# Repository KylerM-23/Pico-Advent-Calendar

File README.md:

# Pico-Advent-Calendar

## Introduction
The 25 Days of Makermas is a Raspberry Pi Pico kit consiting of 25 projects that serve as an introduction to programming and controlling devices with a Raspberry Pi Pico. </br>

[Booklet WIP](https://docs.google.com/document/d/1rmNjlnt3vpmemfZ5pnnCj9qUnz_O2xRp1bQ-7SMrb30/edit?usp=sharing) </br> </br> 
</br> 
 
## Parts Included:

| Item                           | Quantity | | Item                           | Quantity |
| ------------------------------ | -------- |-| ------------------------------ | -------- |
| Pi Pico                        | 1        | | Large Button                   | 3        |
| Makermas PCB                   | 1        | | Large Button Caps              | 3        |
| Wire M-F                       | 1        | | Slide Switch                   | 3        |
| Wire F-F                       | 1        | | Common Anode RGB LED           | 3        |
| Wire M-M                       | 1        | | White LED                      | 10       |
| 10k Potentiometer              | 2        | | Green LED                      | 10       |
| 180 Degree Servo Motor         | 1        | | HC-SR04 Ultrasonic Sensor      | 1        |
| 2.2K Resistors                 | 20       | | PIR Motion Sensor HC-SR501     | 1        |
| 10k Resistors                  | 4        | | TMP1075 I2C Module             | 1        |
| 10k Photoresistor              | 2        | | 1602 I2C LCD                   | 1        |
| 10k Thermistor                 | 2        | | Capacitive Touch Sensor Module | 1        |
| Common Anode 7-Segment Display | 2        | | 16 Pin IC Sockets              | 3        |
| 220 Ohm Resistor Array         | 4        | | 2 Pin Male Header              | 2        |
| SN74HC595 IC                   | 3        | | 2 Pin Jumper                   | 2        |
| 0.1uF Capacitor                | 4        | | 3 Pin Male Header              | 4        |
| Passive (Transducer) Buzzer    | 2        | | Popsicle Stick                 | 3        |
| Active (Indicator) Buzzer      | 2        | | Rubber Band                    | 3        |
| Small Button                   | 10       | | Micro USB Cable                | 1        |
| 3 Pin Female Header            | 2        | | 4 Pin Male Header              | 3        |
| 4 Pin Female Header            | 3        | | 5 Pin Female Header            | 3        |
| 20 Pin Female Header           | 3        | | 5 Pin Female Header            | 5        |
| Nylon Standoffs M3 x 20MM      | 5        |

## Table of Contents
- [Day 1](#day1)
- [Day 2](#day2)
- [Day 3](#day3)
- [Day 4](#day4)
- [Day 5](#day5)
- [Day 6](#day6)
- [Day 7](#day7)
- [Day 8](#day8)
- [Day 9](#day9)
- [Day 10](#day10)
- [Day 11](#day11)
- [Day 12](#day12)
- [Day 13](#day13)
- [Day 14](#day14)
- [Day 15](#day15)
- [Day 16](#day16)
- [Day 17](#day17)
- [Day 18](#day18)
- [Day 19](#day19)
- [Day 20](#day20)
- [Day 21](#day21)
- [Day 22](#day22)
- [Day 23](#day23)
- [Day 24](#day24)
- [Day 25](#day25)

## Day 1: Setup 
1. [Thonny IDE](#day1_thonny)
   1. Install Thonny
   2. Download Pi Pico Firmware
   3. Run Test Program
2. [The Pi Pico Pinout](#day1_pinout)
   1. Pinout
   2. Identify GPIO pin for LED
3. [Controlling the onboard LED](#day1_demo)
  
### Thonny IDE 
Go to the [Thonny](https://thonny.org/) website and download the free IDE. Thonny was chosen because it has features that make it easier to program with the pico and installing the firmware.

After opening Thonny, go to _Run_ -> _Configure Interpreter_                                                                   </br> </br> 
From the Interpreter Menu Select _MicroPython (Raspberry Pi Pico)_ and click on __Install or update MicroPython__              </br>  </br> 
Copy the following settings to install the Pi Pico Firmware. _If you have a different Pico model, choose the proper variant._  </br> </br> 

The Pico should be ready to go. </br>

We can now use the shell and write the hardest line of code ever. </br> </br> 

### Pico Pinout  
Microcontrollers have multiple pins that have multiple functions on each. Most pins are general purpose input outpute (GPIO) pins that can be configure to output signals/data or input (recieve) signals/data. The other pins are power pins or serve special functions.
 - The power pins are VBUS (5V from the USB), 3V3 (3.3V), and GND. The other pins are power input or other functons.

Many of the GPIO pins have multiple functions that can only be used on that pin. For example Pin 32 has GP27, ADC1, and I2C1 SDA for its functions. Programmers can choose which function they want to use on each pin. How you use each pin will vary on what pin functions you need.
- For example if you need a lot of ADC functions, it may be better to use another pin's I2C function and dedicate Pin 32 to ADC.

The image below shows all the pins on the pico with their respective features. </br>  </br> 

### Controlling the onboard LED 
Day1.py toggles the onboard LED and you can vary the speed at which the LED blinks. If you make the time fast enough the LED will appear constantly illuminated and you cannot see it turning off.

</br> 

## Day 2: Soldering 
Day 2 introduces the main PCB and the header pins, and LED Checker/ Status Light are soldered in.

</br> 

## Day 3: Controlling an External LED 
Day 3 invovles controlling an LED with the GPIO pins and explaining GPIO pins in a little more detail in addition to the various methods to control the LED.

</br> 

## Day 4: Reading Inputs From a Button 
Day 4 continues the basics of GPIO inputs covering digital logic levels and reading inputs from a push button.

</br> 

## Day 5: Slide Switch 
Day 5 introduces slide switches and using internal pull-up/down resistors.

</br> 

## Day 6: Active Buzzer 
Day 6 introduces buzzers and how they create sound.

</br> 

## Day 7: Capacitive Touch Sensor 
Day 7 introduces capacitive touch sensors and uses them to create a tapping game. Interrupts are introduced here.

</br> 

## Day 8: RGB LED 
Day 8 introduces RGB LEDs and LED configurations like common anode. The first class is created here.

</br> 

## Day 9: Button Matrix 
Day 9 sees the creation of a class to handle reading the inputs of 4 buttons.

</br> 

## Day 10: Simon Says 
Day 10 is the first big system lesson that has the button matrix, RGB LED, and buzzer used to create a game of simon says!

</br> 

## Day 11: Analog Inputs With a Potentiometer 
Day 11 introduces analog inputs and reading them with the ADC on the pico. A potentiometer is measured as an example.

</br> 

## Day 12: PWM 
Day 12 introduces PWM and how to creates an effective analog voltage for us to control devices like an LED.

</br> 

## Day 13: Rainbow RGB LED 
Day 13 sees PWM used with the RGB LED to create various colors and sweep through the visible color spectrum.

</br> 

## Day 14: Servo Motor 
Day 14 utilizes PWM to control a servo motor and walks through the process of creating the code needed to control PWM devices.

</br> 

## Day 15: Passive Buzzer 
Day 15 sees the user creating a music by using PWM to produce different pitched notes.

</br> 

## Day 16: PIR Motion Sensor 
Day 16 introduces a PIR motion sensor and uses it to detect motion nearby.

</br> 

## Day 17: Ultrasonic Sensor 
Day 17 introduces the ultrasonic distance sensor.

</br> 

## Day 18: Proimity Gate 
Day 18 allows the user to create an arm gate that opens when the ultrasonic sensor and or motion sensor detect someone approaching it. Day 18 comes with a popsicle stick and rubber band to create the "arm".

</br> 

## Day 19: Photoresistor 
Day 19 introduces the photoresistor and how to estimate the amount of light to control other devices.

</br> 

## Day 20: Thermistor 
Day 20 introduces the thermistor and how to measure the ambient temperature.

</br> 

## Day 21: Snowflake Display 
Day 21 introduces the 74HC595 shift register to control multiple LEDs (snowflake display) with less pins. 

</br> 

## Day 22: 7-Segment Display 
Day 22 has the user daisy chain shift registers to control multiple LED displays. The LED display for ths lesson is a 7-segment display.

</br> 

## Day 23: TMP1075 
Day 23 introduces I2C devices and uses the TMP1075 to measure temperature.

</br> 

## Day 24: 1602 LCD 
Day 24 introduces the 1602 LCD and using multiple I2C devices on the same bus.

</br> 

## Day 25: Spread Holiday Cheer 
On Day 25 you must express your holiday cheer. How you do so is left to you. You have plenty of tools. Good luck! </br>
To give you a place to start. One idea is to have a light show with the snowflake display while Christmas music plays on the buzzer (you can also control both buzzers).

</br> 
#Thanks
This project is ongoing and will likely continue to change. Thanks for checking it out.

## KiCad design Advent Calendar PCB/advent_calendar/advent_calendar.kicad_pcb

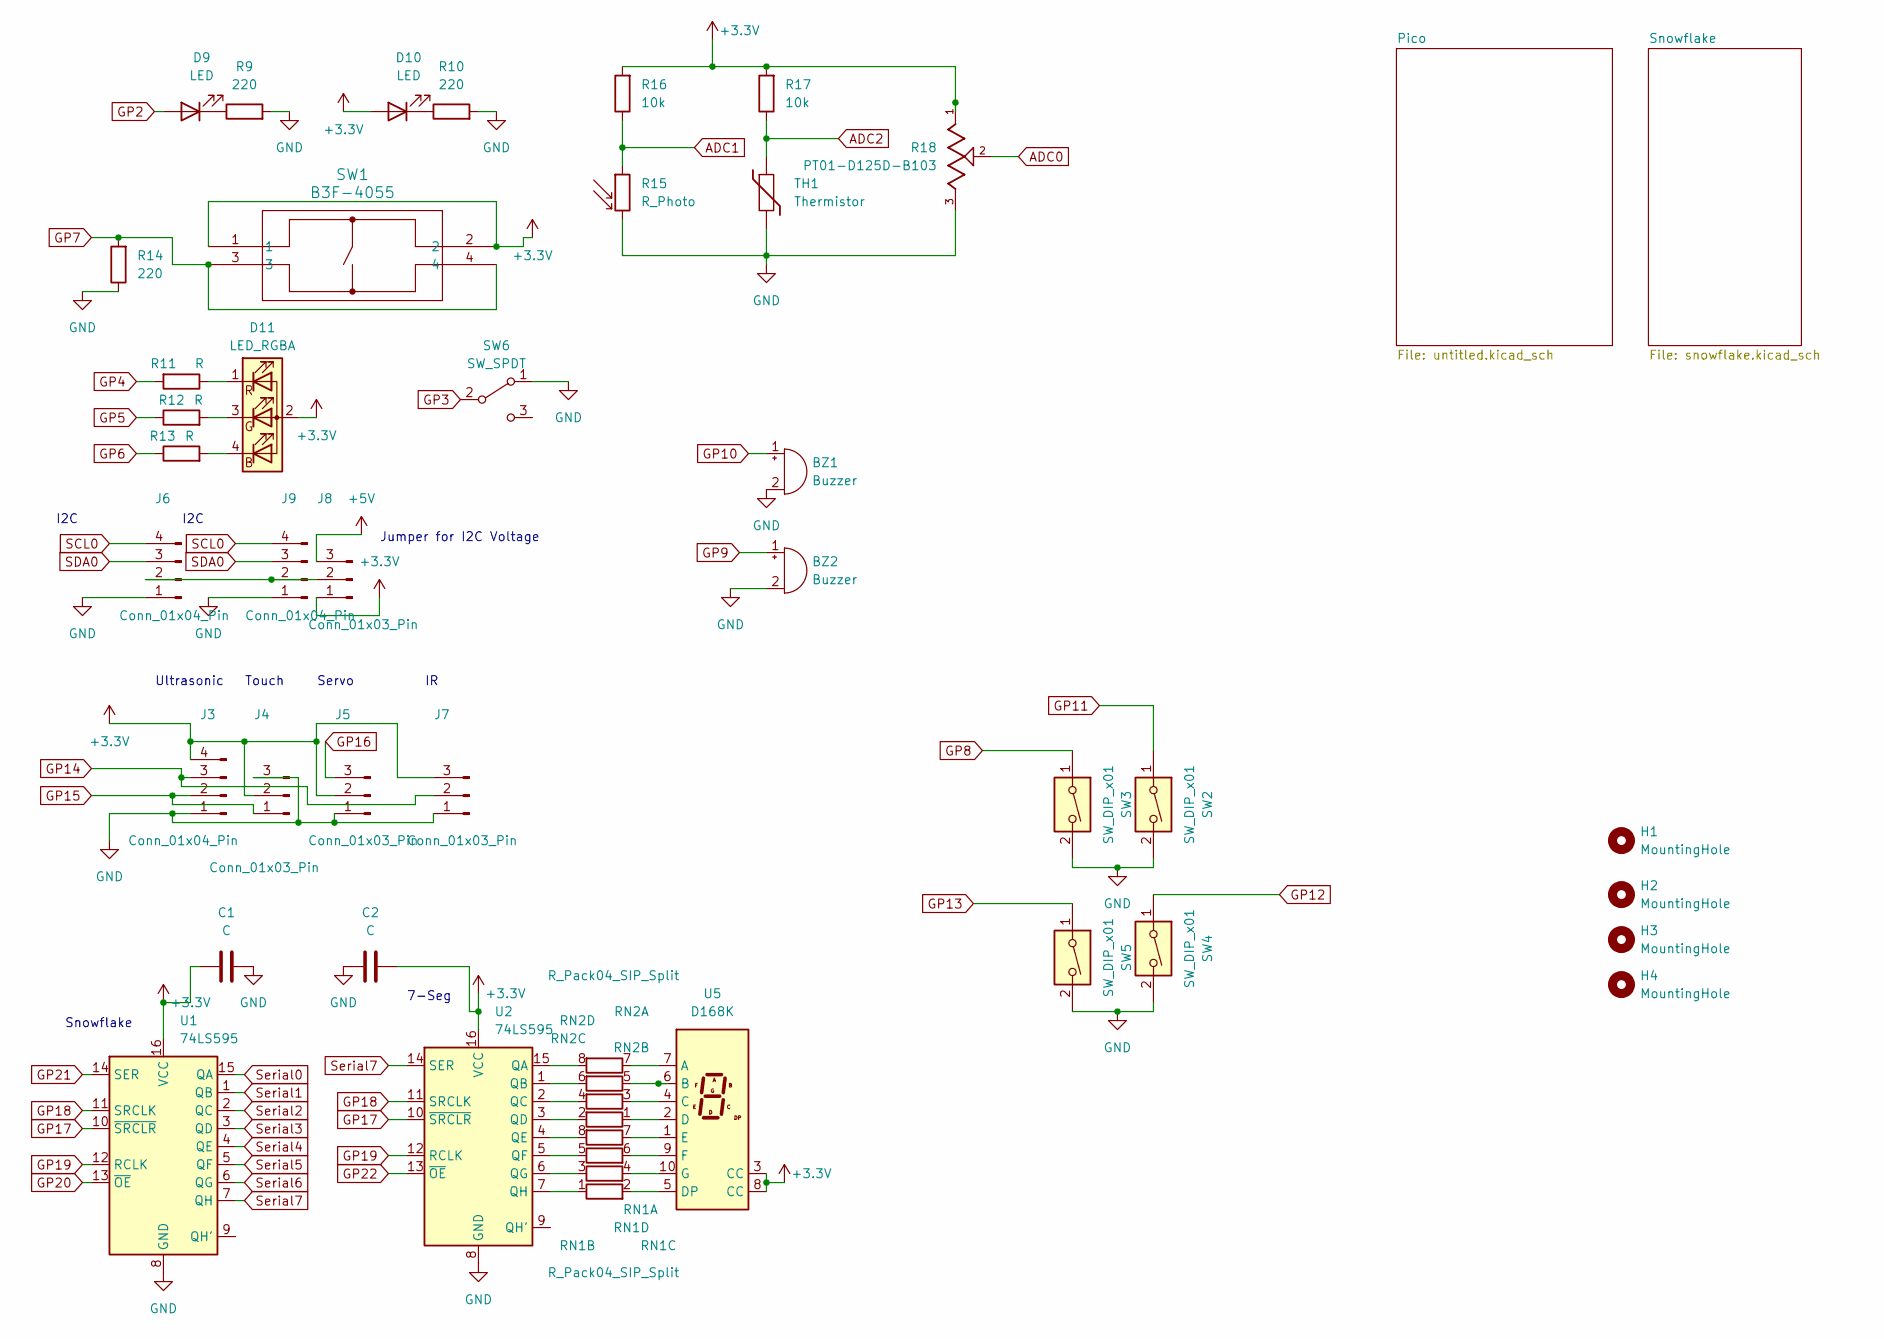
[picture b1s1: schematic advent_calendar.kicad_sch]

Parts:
BZ1, BZ2: Buzzer; Buzzer_12x9.5RM7.6
C1, C2: C; C_Rect_L4.0mm_W2.5mm_P2.50mm
D9, D10: LED; LED_D5.0mm
D11: LED_RGBA; LED_D5.0mm-4_RGB_Wide_Pins
H1, H2, H3, H4: MountingHole; MountingHole_3mm
J3, J6, J9: Conn_01x04_Pin; PinHeader_1x04_P2.54mm_Vertical
J4, J5, J7, J8: Conn_01x03_Pin; PinHeader_1x03_P2.54mm_Vertical
R9, R10, R14: 220; R_Axial_DIN0207_L6.3mm_D2.5mm_P10.16mm_Horizontal
R11, R12, R13: R; R_Axial_DIN0207_L6.3mm_D2.5mm_P10.16mm_Horizontal
R15: R_Photo; R_LDR_7x6mm_P5.1mm_Vertical
R16, R17: 10k; R_Axial_DIN0207_L6.3mm_D2.5mm_P10.16mm_Horizontal
R18: PT01-D125D-B103; TRIM_PT01-D125D-B103; PARTREV 1.0
RN1, RN2: R_Pack04_SIP_Split; R_Array_SIP8
SW1: B3F-4055; SW_B3F-4050_OMR
SW2, SW3, SW4, SW5: SW_DIP_x01; SW_PUSH_6mm
SW6: SW_SPDT; PinHeader_1x03_P2.54mm_Vertical
TH1: Thermistor; PinHeader_1x02_P2.54mm_Vertical
U1, U2: 74LS595; DIP-16_W7.62mm
U5: D168K; D1X8K

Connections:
+3.3V: C1.1, C2.2, D10.2 (A), D11.2, J3.4, J4.2, J5.2, J7.3, J8.1, R16.2, R17.2, R18.1, SW1.1, SW1.2, U1.16 (VCC), U2.16 (VCC), U5.3 (CC), U5.8 (CC); also elsewhere on the board
+5V: J8.3; also elsewhere on the board
ADC0: R18.2; also elsewhere on the board
ADC1: R15.1, R16.1; also elsewhere on the board
ADC2: R17.1, TH1.1; also elsewhere on the board
GND: BZ1.2 (+), BZ2.2 (+), C1.2, C2.1, J3.1, J4.3, J5.1, J6.1, J7.1, J9.1, R9.2, R10.2, R14.1, R15.2, R18.3, SW2.2, SW3.2, SW4.2, SW5.2, SW6.1 (A), TH1.2, U1.8 (GND), U2.8 (GND); also elsewhere on the board
GP2: D9.2 (A); also elsewhere on the board
GP3: SW6.2 (B); also elsewhere on the board
GP4: R11.2; also elsewhere on the board
GP5: R12.1; also elsewhere on the board
GP6: R13.1; also elsewhere on the board
GP7: R14.2, SW1.3, SW1.4; also elsewhere on the board
GP8: SW3.1; also elsewhere on the board
GP9: BZ2.1 (-); also elsewhere on the board
GP10: BZ1.1 (-); also elsewhere on the board
GP11: SW2.1; also elsewhere on the board
GP12: SW4.1; also elsewhere on the board
GP13: SW5.1; also elsewhere on the board
GP14: J3.3, J7.2; also elsewhere on the board
GP15: J3.2, J4.1; also elsewhere on the board
GP16: J5.3; also elsewhere on the board
GP17: U1.10 (~SRCLR), U2.10 (~SRCLR); also elsewhere on the board
GP18: U1.11 (SRCLK), U2.11 (SRCLK); also elsewhere on the board
GP19: U1.12 (RCLK), U2.12 (RCLK); also elsewhere on the board
GP20: U1.13 (~OE); also elsewhere on the board
GP21: U1.14 (SER); also elsewhere on the board
GP22: U2.13 (~OE); also elsewhere on the board
unnamed: D9.1 (K), R9.1
unnamed: D10.1 (K), R10.1
unnamed: D11.3, R12.2
unnamed: D11.4, R13.2
unnamed: D11.1 (RK), R11.1
unnamed: J6.2, J8.2, J9.2
unnamed: RN1.1 (R1.1), U2.7 (QH)
unnamed: RN1.2 (R1.2), U5.5 (DP)
unnamed: RN1.3 (R2.1), U2.6 (QG)
unnamed: RN1.4 (R2.2), U5.10 (G)
unnamed: RN1.5 (R3.1), U2.5 (QF)
unnamed: RN1.6 (R3.2), U5.9 (F)
unnamed: RN1.7 (R4.1), U5.1 (E)
unnamed: RN1.8 (R4.2), U2.4 (QE)
unnamed: RN2.1 (R1.1), U5.2 (D)
unnamed: RN2.2 (R1.2), U2.3 (QD)
unnamed: RN2.3 (R2.1), U5.4 (C)
unnamed: RN2.4 (R2.2), U2.2 (QC)
unnamed: RN2.5 (R3.1), U5.6 (B)
unnamed: RN2.6 (R3.2), U2.1 (QB)
unnamed: RN2.7 (R4.1), U5.7 (A)
unnamed: RN2.8 (R4.2), U2.15 (QA)
SCL0: J6.4, J9.4; also elsewhere on the board
SDA0: J6.3, J9.3; also elsewhere on the board
Serial0: U1.15 (QA); also elsewhere on the board
Serial1: U1.1 (QB); also elsewhere on the board
Serial2: U1.2 (QC); also elsewhere on the board
Serial3: U1.3 (QD); also elsewhere on the board
Serial4: U1.4 (QE); also elsewhere on the board
Serial5: U1.5 (QF); also elsewhere on the board
Serial6: U1.6 (QG); also elsewhere on the board
Serial7: U1.7 (QH), U2.14 (SER); also elsewhere on the board

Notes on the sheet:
Ultrasonic
Servo
Touch
I2C
Snowflake
7-Seg
Jumper for I2C Voltage

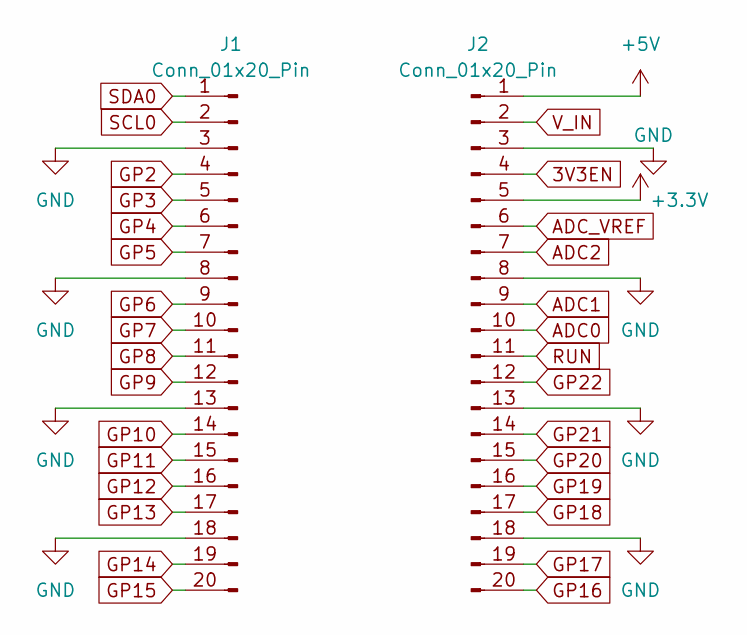
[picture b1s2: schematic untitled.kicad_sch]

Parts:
J1, J2: Conn_01x20_Pin; PinHeader_1x20_P2.54mm_Vertical

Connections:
3V3EN: J2.4
+3.3V: J2.5; also elsewhere on the board
+5V: J2.1; also elsewhere on the board
ADC0: J2.10; also elsewhere on the board
ADC1: J2.9; also elsewhere on the board
ADC2: J2.7; also elsewhere on the board
ADC_VREF: J2.6
GND: J1.3, J1.8, J1.13, J1.18, J2.3, J2.8, J2.13, J2.18; also elsewhere on the board
GP2: J1.4; also elsewhere on the board
GP3: J1.5; also elsewhere on the board
GP4: J1.6; also elsewhere on the board
GP5: J1.7; also elsewhere on the board
GP6: J1.9; also elsewhere on the board
GP7: J1.10; also elsewhere on the board
GP8: J1.11; also elsewhere on the board
GP9: J1.12; also elsewhere on the board
GP10: J1.14; also elsewhere on the board
GP11: J1.15; also elsewhere on the board
GP12: J1.16; also elsewhere on the board
GP13: J1.17; also elsewhere on the board
GP14: J1.19; also elsewhere on the board
GP15: J1.20; also elsewhere on the board
GP16: J2.20; also elsewhere on the board
GP17: J2.19; also elsewhere on the board
GP18: J2.17; also elsewhere on the board
GP19: J2.16; also elsewhere on the board
GP20: J2.15; also elsewhere on the board
GP21: J2.14; also elsewhere on the board
GP22: J2.12; also elsewhere on the board
RUN: J2.11
SCL0: J1.2; also elsewhere on the board
SDA0: J1.1; also elsewhere on the board
V_IN: J2.2

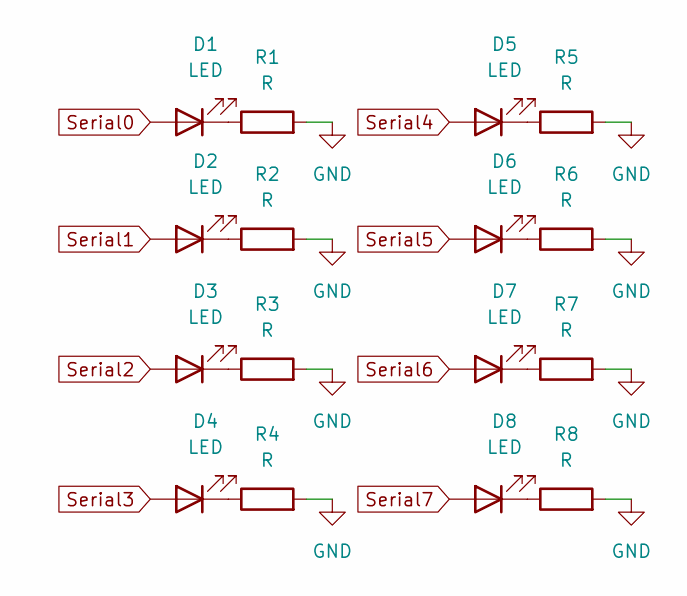
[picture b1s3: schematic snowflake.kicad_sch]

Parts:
D1, D2, D3, D4, D5, D6, D7, D8: LED; LED_D5.0mm
R1, R2, R3, R4, R5, R6, R7, R8: R; R_Axial_DIN0207_L6.3mm_D2.5mm_P10.16mm_Horizontal

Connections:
GND: R1.2, R2.2, R3.2, R4.2, R5.2, R6.2, R7.2, R8.2; also elsewhere on the board
unnamed: D1.1 (K), R1.1
unnamed: D2.1 (K), R2.1
unnamed: D3.1 (K), R3.1
unnamed: D4.1 (K), R4.1
unnamed: D5.1 (K), R5.1
unnamed: D6.1 (K), R6.1
unnamed: D7.1 (K), R7.1
unnamed: D8.1 (K), R8.1
Serial0: D1.2 (A); also elsewhere on the board
Serial1: D2.2 (A); also elsewhere on the board
Serial2: D3.2 (A); also elsewhere on the board
Serial3: D4.2 (A); also elsewhere on the board
Serial4: D5.2 (A); also elsewhere on the board
Serial5: D6.2 (A); also elsewhere on the board
Serial6: D7.2 (A); also elsewhere on the board
Serial7: D8.2 (A); also elsewhere on the board

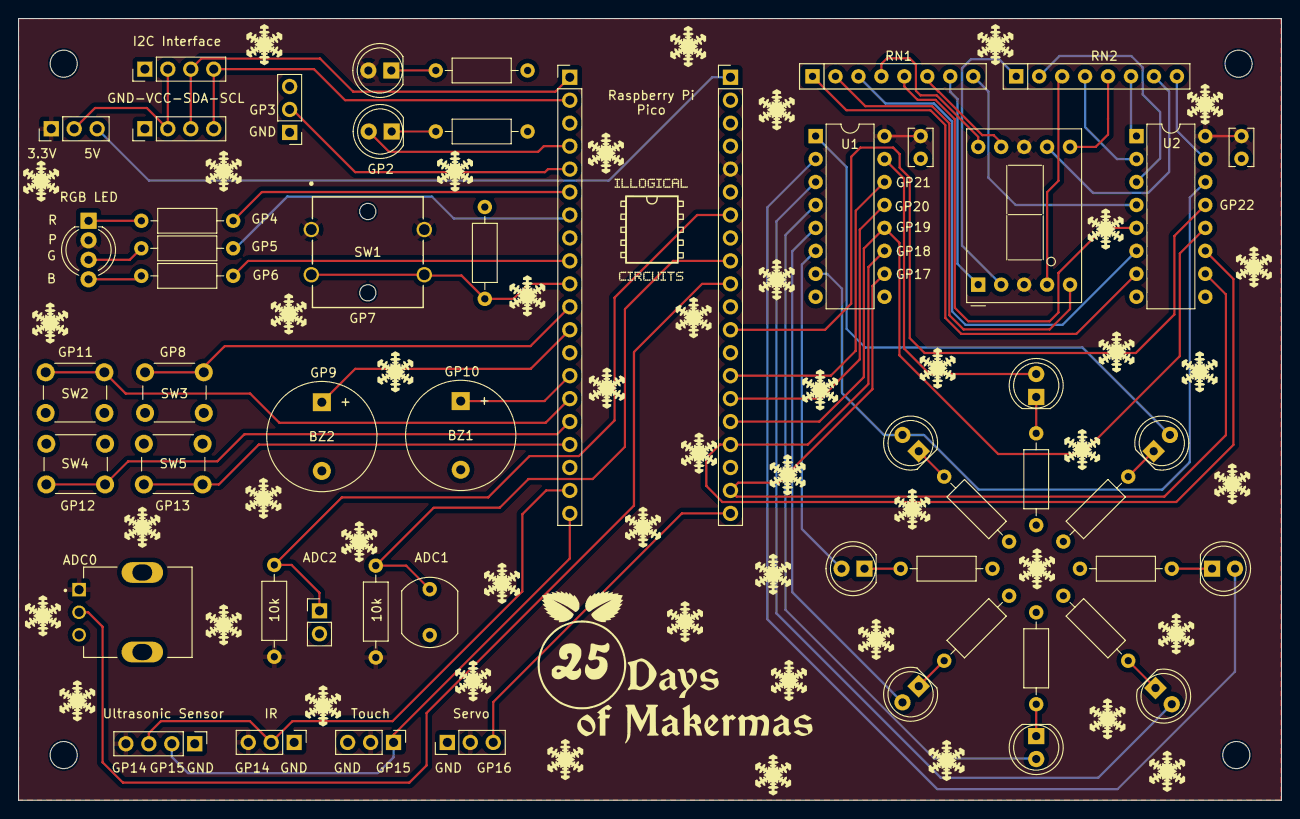
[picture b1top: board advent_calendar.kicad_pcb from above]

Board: 2 copper layers, 139.8 x 86.5 mm, 58 parts (0 on the bottom side), 67 nets.

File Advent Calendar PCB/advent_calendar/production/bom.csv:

Designator,Footprint,Quantity,Value,LCSC Part #
"BZ1, BZ2",Buzzer_12x9.5RM7.6,2,Buzzer,
"C1, C2",C_Rect_L4.0mm_W2.5mm_P2.50mm,2,C,
"D1, D10, D2, D3, D4, D5, D6, D7, D8, D9",LED_D5.0mm,10,LED,
D11,LED_D5.0mm-4_RGB_Wide_Pins,1,LED_RGBA,
"H1, H2, H3, H4",MountingHole_3mm,4,MountingHole,
"J1, J2",PinHeader_1x20_P2.54mm_Vertical,2,Conn_01x20_Pin,
"J3, J6, J9",PinHeader_1x04_P2.54mm_Vertical,3,Conn_01x04_Pin,
"J4, J5, J7, J8",PinHeader_1x03_P2.54mm_Vertical,4,Conn_01x03_Pin,
"R1, R11, R12, R13, R2, R3, R4, R5, R6, R7, R8",R_Axial_DIN0207_L6.3mm_D2.5mm_P10.16mm_Horizontal,11,R,
"R10, R14, R9",R_Axial_DIN0207_L6.3mm_D2.5mm_P10.16mm_Horizontal,3,220,
R15,R_LDR_7x6mm_P5.1mm_Vertical,1,R_Photo,
"R16, R17",R_Axial_DIN0207_L6.3mm_D2.5mm_P10.16mm_Horizontal,2,10k,
R18,TRIM_PT01-D125D-B103,1,PT01-D125D-B103,
"RN1, RN2",R_Array_SIP8,2,R_Pack04_SIP_Split,
SW1,SW_B3F-4050_OMR,1,B3F-4055,
"SW2, SW3, SW4, SW5",SW_PUSH_6mm,4,SW_DIP_x01,
SW6,PinHeader_1x03_P2.54mm_Vertical,1,SW_SPDT,
TH1,PinHeader_1x02_P2.54mm_Vertical,1,Thermistor,
"U1, U2",DIP-16_W7.62mm,2,74LS595,
U5,D1X8K,1,D168K,

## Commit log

2024-11-03 Initial Upload
    Adding the current files for the Advent Calendar
2024-11-09 Rename Pi_Pico_Advent_Calendar.jpg to images/Pi_Pico_Advent_Calendar.jpg
2024-11-09 Added Images
2024-11-09 Moved Files
2024-11-09 new pics
2024-11-09 Update README.md
    Added Day 1 information to get started
2024-11-09 Update README.md
    remember kids # is kinda important
2024-11-13 day18 code
    added a starter day18 code
2024-11-14 added days 15,18,23
    added code for those days
2024-11-21 Added KiCad PCB
    Added KiCad PCB
2024-12-04 Update WeWishYouAMerryChristmas.py
    removed a local debug import
2025-01-21 Updated lesson order
    Moved Buzzer, Touch Sensor, and Slide Switch Lessons.
    Expanded upon slide switch to include debouncing topic.
    Moving the short buzzer lesson to lower numbers will make more sense.
